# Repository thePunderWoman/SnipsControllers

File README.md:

<h1 align="center">The Snips Controllers</h1>

<p align="center">
  Wireless handheld controllers for R2-D2 droid operation, built to work with the
  <a href="https://github.com/thePunderWoman/Amidala">Amidala</a> control system and firmware.
</p>

<p align="center">
  
</p>

## Status

**Awaiting prototype PCBs.**

The Stackup circuit design, part matching, and layout review are complete; boards are in the ordering/fab pipeline. See [PCB/v1.x/README.md](PCB/v1.x/README.md) for the full hardware writeup and [PCB/v1.x/design-review-2026-08-23.md](PCB/v1.x/design-review-2026-08-23.md)
for the latest design review. PCBs will likely arrive middle to late September. Once the controllers have been validated, we'll start ordering larger runs and make them available for people to buy.

## What they are

The Snips controllers are dual small handheld controllers for driving your droid
builds. These controllers are intended to be small, but powerful controllers that
can be configured via Amidala to do whatever you prefer to do.

## What they offer

Each Snips controller offers 6 face buttons, 2 side buttons on each side, 1 bumper
button, and a precision hall effect analog trigger. They utilize standard thumbsticks
and are specifically designed to work with either gulikit hall effect or tmr kits,
making sure you have no stick drift over time.

Combining all buttons, including center stick, that's 13 button options per controller. Plus, through Amidala each button can support regular press, alt button press, double press, and long press. All told, you have currently up to **52** different programmable options per controller!

Each controller also has a small OLED screen just above the thumbsticks for as much
info as you'd like to see, like power levels, which hand the controller is for, which
droid, volume levels, etc.

## Communication

These controllers are designed to work with Xbee3 modules for long distance secure
communication, but also, since they are powered by ESP32-S3-WROOM-1 modules, they also
support bluetooth and ESP-Now for connectivity. They will be able to swap between droids, as well.

## Batteries

Each controller runs on a single swappable 14500 lithium ion cell (3.7V Li-ion, not 3.2V LiFePO4). We're using 1300 mAh Keeppower cells. The controllers have a built in charging circuit. So you can charge them via USB-C, or just plain swap mid-event if they run out.

Based on datasheet figures (not yet measured on real hardware), a controller with an XBee3 Pro draws about 100 mA, so a 1300 mAh cell should last roughly 11–12 hours of use, or about 8 hours in the worst case.

## Case

The controller case, aka how it looks and feels in the hand is still to be designed, but will be open source, allowing you to make it as unique to your build as you'd like.

## Estimated price

This is yet to be determined since we're so early in the prototype stage, but the pricing will be fully transparent. We will likely try to bundle two controllers with an Amidala board, and hopefully close to at cost with a small donation to charity included.

## Repository layout

| Path | Contents |
|---|---|
| [`src/`](src) | ESP32-S3 firmware (PlatformIO) |
| [`test/`](test) | Native unit tests (no hardware required) |
| [`PCB/`](PCB) | Stackup circuit design, KiCad layout, GPIO reference, and design notes |
| [`scripts/`](scripts) | BOM/part-matching tooling |

## Development

Requires [PlatformIO](https://platformio.org/) (CLI or IDE extension).

```bash
# Build the firmware for V1.x boards (the default)
pio run

# Build the firmware for V2 boards
pio run -e esp32s3_v2

# Run unit tests (no hardware required)
pio test -e native
```

See [CONTRIBUTING.md](CONTRIBUTING.md) for the full contribution workflow.

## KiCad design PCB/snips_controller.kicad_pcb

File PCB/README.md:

# Snips Controller PCB

A wireless handheld controller for R2-D2 droid operation, designed for use at public events and conventions. Communicates with the droid via XBee3 Zigbee radio in a packetized state-report architecture.

The electrical design is in [Stackup KDL](stackup/board.kdl), using the pinned
Stackup library plus a [local thumbstick model](stackup/parts.kdl). The existing [KiCad PCB](snips_controller.kicad_pcb) is linked
through `snips_controller.stackup_sch`; sync it with the Stackup KiCad plugin. Run
`stackup check PCB/stackup/board.kdl` from the repository root before syncing.

## Hardware Overview

| Component | Part | Notes | Layout diagram |
|---|---|---|---|
| MCU | ESP32-S3-WROOM-1 module | Pre-certified: integrated flash, crystal, WiFi/BT radio + antenna. Same MCU family as Amidala. See `GPIO_table.md` for the full support circuitry | — |
| Display | SSD1306 1.3" OLED | 128x64, monochrome, I2C | — |
| Radio | XBee3 Pro (XB3-24Z8UT) | Zigbee 3.0 firmware, U.FL, +19 dBm, SPI mode, THT socket (proto) | — |
| Hall trigger | DRV5055A2QDBZR (SOT-23) | Ratiometric linear hall effect, 3.3V. On the bottom of the board under the trigger magnet; senses the field perpendicular to the board. Trigger calibration accepts either magnet polarity | — |
| Thumbstick | GuliKit hall effect module | Native 3.3V, analog X/Y + click | — |
| Buttons | Omron B3F series | Tactile momentary clicky | — |
| RGB LED | SK6812 NeoPixel-compatible | RMT-driven status indicator; specified supply begins at 3.7 V, but board supplies 3.3 V | — |
| Charger | bq25185 | USB/DC input, power path, 4.2V/500mA | [diagram](diagrams/power_charger_layout.md) |
| Buck | TLV62569 | 3.3V output, 1A | [diagram](diagrams/power_buck_layout.md) |
| Battery | 14500 Li-ion (Keeppower 1300 mAh) | Swappable single cell; 500 mA charge ≈ 0.38C | — |
| Power switch | DMG2305UX + 2N7002 | Soft latch, hybrid hardware+firmware | [diagram](diagrams/power_control_layout.md) |

## Layout Diagrams

Suggested top-copper floorplans for the three sheets with real layout
stakes — a switching regulator, a linear charger with a thermal pad, and
the transistor carrying the whole board's current. Each is checked
against the actual component datasheet, not just the schematic. See
[`diagrams/README.md`](diagrams/README.md) for the full list and how the
files are organized.

- [Buck converter](diagrams/power_buck_layout.md) — `/Power_Buck/*` nets in Stackup
- [Charger](diagrams/power_charger_layout.md) — `/Power_Charger/*` nets in Stackup
- [Power latch](diagrams/power_control_layout.md) — `/Power_Control/*` nets in Stackup

## GPIO Assignment

> See `GPIO_table.md` for the full pin-by-pin table, including
> ESP32-S3-WROOM-1 support circuitry — this section is a summary.

### Reserved — Do Not Use
| Pin | Reason |
|---|---|
| 1, 40, 41 | GND |
| 2 | 3V3 |
| 3 (EN) | Reset/enable, pulled up via R_EN_PU |
| 13 (USB_D-) | Native USB |
| 14 (USB_D+) | Native USB |
| 27 (GPIO0/BOOT) | Boot strapping pin, pulled up via R_BOOT_PU + button |
| 26-32 (internal) | Internal SPI flash — not present on this module at all |
| 33-34 (internal) | Not broken out on the WROOM-1 module |
| 8 (GPIO15) | XBee SPI_ATTN — data-ready interrupt |
| 22 (GPIO18) | XBee ON_SLEEP status input |

Usable with care (strapping pins, sampled at boot): 15 (GPIO3), 16 (GPIO46), 26 (GPIO45).
Clean spares (default JTAG): 34-35 (GPIO41-42). 32/33 from the same group are used by BTN_VOL_DN/BTN_VOL_UP.

The module integrates the WiFi/BT radio, antenna, flash, and crystal
internally — no external wireless component, no bit-banged interface
consuming GPIO, unlike the bare-RP2350A design this replaced.

### SPI (XBee)
| Function | Pin |
|---|---|
| XBee SCK | 18 |
| XBee MOSI | 19 |
| XBee MISO | 20 |
| XBee CS | 21 |
| XBee ON_SLEEP | 22 |
| XBee SPI_ATTN | 8 |

### I2C (OLED)
| Function | Pin |
|---|---|
| SDA | 12 |
| SCL | 17 |

### ADC — ADC1 only (ADC2 is unusable while WiFi is active)
| Function | Pin |
|---|---|
| Analog trigger (DRV5055) | 4 |
| Thumbstick X (GuliKit) | 5 |
| Thumbstick Y (GuliKit) | 6 |
| VSYS battery sense | 7 |

### Digital Inputs / Outputs
| Function | Pin | Notes |
|---|---|---|
| Vol up | 33 | Active low, internal pull-up |
| Vol down | 32 | Active low, internal pull-up |
| Trigger up (mirrored VOL pair, opposite-handed variant) | 9 | Active low, internal pull-up |
| Trigger down (mirrored VOL pair, opposite-handed variant) | 10 | Active low, internal pull-up |
| Digital trigger (bumper) | 11 | Active low, internal pull-up. Two switches in parallel (SW_TRIG_DIG1/2), one at each end of the top edge, so the bumper presses from either side |
| Thumbstick click (KEY) | 23 | Active low, internal pull-up |
| Macro buttons 1-6 | 24, 25, 28, 29, 30, 31 | Active low, internal pull-up — direct-wired, no scan matrix |
| Power button sense | 38 | Input, 3-second hold detect |
| Charge status STAT1 | 39 | Open-drain, 10kΩ pull-up to 3V3 |
| Power latch hold | 36 | Output, HIGH on boot to hold latch |
| RGB LED DIN (SK6812) | 37 | RMT-driven |

### Macro Buttons — Direct-Wired, No Scan Matrix
6 macro buttons, each on its own GPIO with an internal pull-up. No
anti-ghosting diodes or scan firmware needed — ESP32-S3-WROOM-1 has
enough spare GPIO (roughly 8) that the 1-pin savings a 2x3 matrix would
give isn't worth the added complexity, unlike the bare-RP2350A design
(only 1 spare pin) this replaced.

### Spare GPIO
Pins 34-35 (default JTAG, clean) and 15/16/26 (strapping, usable with care).
32/33 from the same JTAG group are used by BTN_VOL_DN/BTN_VOL_UP.

---

## MCU Support Circuitry (ESP32-S3-WROOM-1)

Far simpler than the bare-RP2350A design it replaced — the module
integrates flash, crystal, and the WiFi/BT radio + antenna internally.
What's left: EN pull-up, BOOT pull-up + button, USB series resistors,
3V3 decoupling, and the VSYS battery-sense divider — all standard
ESP32-S3 practice, matching Espressif's own reference designs. See
`GPIO_table.md` for the full component list.

**No longer needed at all:** external QSPI flash chip, crystal + load
caps, core-regulator LC filter, ADC_AVDD RC filter, per-pin IOVDD/DVDD
decoupling network, separate wireless module + its bit-banged interface
+ antenna licensing question.

> **Layout note:** the module's footprint includes the required antenna
> keepout area — keep copper/components out of it per the module's
> datasheet. Much simpler than a custom PCB trace antenna, but still a
> real layout-stage requirement.

---

## Passives & Support Components

### Decoupling Caps
| Component | Value | Notes |
|---|---|---|
| DRV5055 VCC | 100nF ceramic | Close to supply pin |
| GuliKit VCC | 100nF ceramic | Close to supply pin |
| SK6812 VCC | 100nF ceramic | Close to supply pin |
| bq25185 VIN | 10µF + 100nF ceramic | X7R/X5R, 25V rated |
| bq25185 SYS | 10µF + 100nF ceramic | X7R/X5R, 25V rated |
| bq25185 BAT | 10µF ceramic | |
| TLV62569 VIN | 10µF ceramic | |
| TLV62569 VOUT | 22µF ceramic | |
| ESP32-S3-WROOM-1 3V3 | 10µF + 100nF ceramic | Standard module decoupling |

### Pull-up Resistors
| Signal | Value | Notes |
|---|---|---|
| bq25185 STAT1 | 10kΩ | Open-drain, pull up to 3V3 |
| bq25185 TS/MR | 10kΩ to GND | REQUIRED if no thermistor — floating = no charging |
| XBee RESET | 10kΩ to 3V3 | Plus 100Ω + 100nF RC filter at pin |
| I2C SDA/SCL | 4.7kΩ | **DNP for prototyping** — Adafruit #938 has onboard pull-ups. Populate only on final PCB with bare OLED panel |
| ESP32-S3 EN | 10kΩ to 3V3 | Reset/enable |
| ESP32-S3 GPIO0/BOOT | 10kΩ to 3V3 | Plus button to GND to force UF2/download mode |

### Series Resistors
| Signal | Value | Notes |
|---|---|---|
| SK6812 DIN (pin 37) | 300–500Ω | Signal integrity, place close to pad |
| USB D+/D- (pins 13/14) | 27Ω | Between module and external USB-C connector |

### Direct Buttons (all of them — no matrix)
No external components needed. Wire to GND; enable ESP32-S3 internal
pull-ups in firmware. Applies to vol up/down, digital trigger, stick
click, and all 6 macro buttons.

### XBee
Refer to AmidalaShield V1.2 for XBee3 support circuitry. THT socket for prototyping; update footprint to SMT module for final PCB if size requires.

Beyond the 4-wire SPI bus (SCK/MOSI/MISO/CS) and RESET, three more pins are
wired per Amidala's actual netlist: DTR tied to GND, ON_SLEEP and SPI_ATTN
to pins 22/8. SPI_ATTN in particular is the XBee's data-ready interrupt —
needed for reliable SPI transfers, not just a nice-to-have.

---

## Communication Architecture

Controllers communicate with the droid via XBee3 in **packetized state-report** mode. The ESP32-S3 firmware reads all inputs locally (button states, ADC values for analog trigger and thumbstick) and assembles them into a structured payload transmitted periodically over SPI to the XBee3 radio. The receiving AmidalaShield deserializes the packet and interprets controller state.

This approach is preferred over per-signal transmission as it is more efficient, easier to deserialize, and robust to timing issues.

### Network Configuration
- Each droid has its own coordinator with a unique PAN ID
- All coordinators share the same AES encryption key
- Controllers are configured as sleepy end devices (CE=0, SM=1 pin sleep, ET=4 for a 16-minute parent timeout), set at boot by the firmware. Their parent (normally the droid's coordinator) holds downlinks while a controller sleeps, and the controller polls for them every 100 ms while awake
- "Switch droid" functionality is implemented via XBee API commands to leave the current network and rejoin a different PAN ID on demand
- Active droid name and connection status are shown on the OLED display

---

## Bringup Sequence

Recommended bringup order:
1. ESP32-S3-WROOM-1 alone — verify USB enumeration, flash blink sketch, confirm pin 36 latch hold works
2. OLED on I2C — verify I2C on pins 12/17, get something on screen
3. SK6812 RGB LED — verify RMT output on pin 37, cycle colors
4. Buttons — verify direct inputs on pins 9/10/11/23 and all 6 macro buttons (pins 24/25/28/29/30/31)
5. Charge status — verify STAT1 on pin 39 reads correctly
6. DRV5055 + GuliKit thumbstick — verify ADC1 readings on pins 4/5/6
7. XBee over SPI — verify basic communication

---

## Power Architecture

- Battery → bq25185 (charger + power path, 4.2V VBATREG, 500mA) → TLV62569 (3.3V buck) → ESP32-S3-WROOM-1 3V3 and all 3.3V logic
- Power switch: soft latch (DMG2305UX PFET + 2N7002 NFET) controls TLV62569 EN pin
- Boot: press power button → hardware latch enables 3V3 → ESP32-S3-WROOM-1 boots → pin 36 driven HIGH to hold latch
- Shutdown: firmware detects 3-second hold on pin 38 → graceful shutdown → pin 36 LOW → power cut
- bq25185 STAT1 → pin 39 (open-drain, 10kΩ pull-up to 3V3)
- Battery voltage sense → pin 7 via external R_VSYS1/R_VSYS2 divider (reads VSYS/3 via ADC1)
- ESP32-S3-WROOM-1, DRV5055, and GuliKit thumbstick use the 3V3 rail. The SK6812 also uses it, but its 3.7 V minimum supply makes that LED connection out of specification.

No firmware ADC-gating workaround needed for battery sense — WiFi is
fully on-die on ESP32-S3 and doesn't share any exposed GPIO/ADC path
with the VSYS sense pin, unlike the old bit-banged RP2350+CYW43439
design.

## Power Management

Firmware implements tiered power saving:
- **Active**: full brightness OLED, normal polling rate
- **Idle (short timeout)**: OLED dimmed via SSD1306 contrast command
- **Idle (long timeout)**: OLED off
- **Sleep**: MCU sleep, wake on any button press via GPIO interrupt

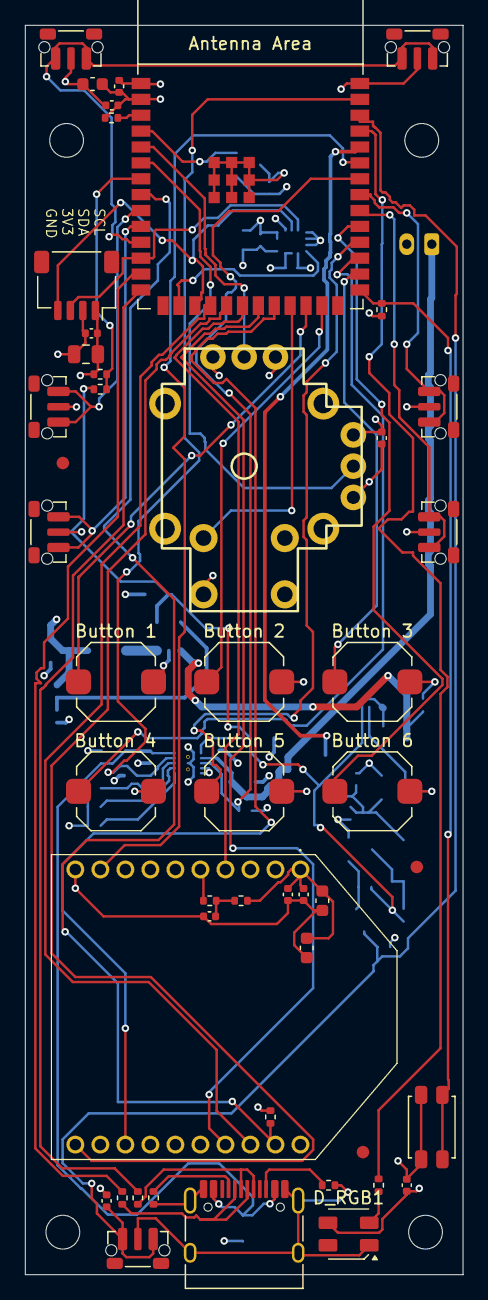
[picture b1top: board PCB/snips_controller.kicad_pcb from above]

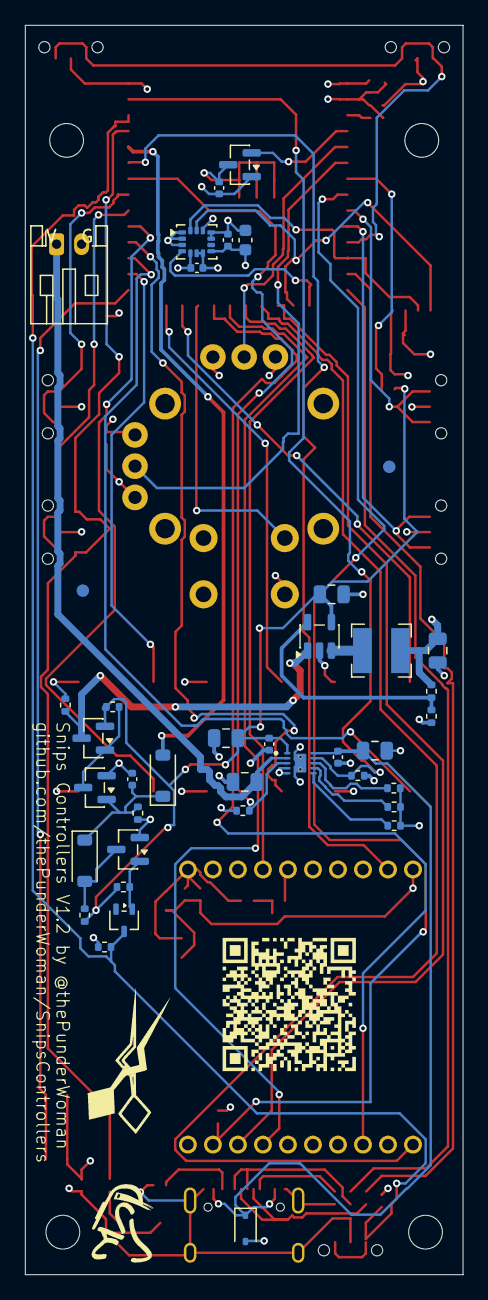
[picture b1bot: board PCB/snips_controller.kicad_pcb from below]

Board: 4 copper layers, 35.0 x 99.9 mm, 95 parts (43 on the bottom side), 57 nets.

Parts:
BT1: PH 2-pin battery RIGHT-ANGLE HORIZONTAL; JST_PH_S2B-PH-K_1x02_P2.00mm_Horizontal
C_3V3_1: 10µF; C_0603_1608Metric
C_3V3_2: 100nF; C_0402_1005Metric
C_3V3_3: 39pF; C_0402_1005Metric
C_BAT1: 10µF; C_0805_2012Metric
C_BUCK_IN1: 10µF; C_0805_2012Metric
C_BUCK_OUT1: 22µF; C_0805_2012Metric
C_DBNC1: 100nF; C_0402_1005Metric
C_HALL1: 100nF; C_0402_1005Metric
C_IMU_1: 100nF; C_0402_1005Metric
C_IMU_2: 2.2µF; C_0603_1608Metric
C_IMU_3: 10nF; C_0402_1005Metric
C_LATCH_G1: 100nF; C_0402_1005Metric
C_OLED_1: 10µF; C_0805_2012Metric
C_OLED_2: 100nF; C_0402_1005Metric
C_RGB1: 100nF; C_0402_1005Metric
C_STICK1: 100nF; C_0402_1005Metric
C_SYS_1: 10µF; C_0805_2012Metric
C_SYS_2: 100nF; C_0402_1005Metric
C_VIN_1: 10µF; C_0805_2012Metric
C_VIN_2: 100nF; C_0402_1005Metric
C_XBEE_RC1: 100nF; C_0402_1005Metric
C_XBEE_VCC1: 100nF; C_0402_1005Metric
C_XBEE_VCC2: 1µF; C_0603_1608Metric
C_XBEE_VCC3: 47pF; C_0402_1005Metric
C_XBEE_VCC4: 10µF; C_0603_1608Metric
D_INV_ISO1: BAT54W-7-F; SOT-323_SC-70
D_OR1, D_OR2: 1N4148W; D_SOD-123
D_RGB1: SK6812MINI-HS-012
D_VBUS_TVS1: TPPESD5V0S1BA; D_SOD-323
FID1, FID2, FID3, FID4, FID5: Fiducial_1mm_Mask2mm
J_STICK1: GuliKit_Thumbstick; GuliKit_HallStick
J_USB1: USB-C; USB_C_Receptacle_HRO_TYPE-C-31-M-12
LOGO1, LOGO2: LOGO
LOGO3: LOGO; R2Builders
L_BUCK1: 2.2µH; L_Bourns-SRN4018
MH1, MH2, MH3, MH4: MountingHole_2.7mm_M2.5
Q_INV1: MMBT3904(RANGE:100-300); SOT-23
Q_LATCH1: AO3400A; SOT-23
Q_PWR1: AO3401A; SOT-23
R_BOOT_PU1: 10kΩ; R_0402_1005Metric
R_BTN_PU1: 100kΩ; R_0402_1005Metric
R_CC1, R_CC2: 5.1kΩ; R_0402_1005Metric
R_EN_PU1: 10kΩ; R_0402_1005Metric
R_FB1: 255kΩ; R_0402_1005Metric
R_FB2: 56.2kΩ; R_0402_1005Metric
R_GATE1: 100kΩ; R_0402_1005Metric
R_INV_BASE1: 100kΩ; R_0402_1005Metric
R_INV_PU1: 100kΩ; R_0402_1005Metric
R_ISET1: 604Ω; R_0402_1005Metric
R_LATCH_G1: 1MΩ; R_0402_1005Metric
R_PWR_EN_PD1: 100kΩ; R_0402_1005Metric
R_RGB1: 470Ω; R_0402_1005Metric
R_STAT1, R_STAT2: 10kΩ; R_0402_1005Metric
R_TS1: 10kΩ; R_0402_1005Metric
R_USB_DM1: 27Ω; R_0402_1005Metric
R_USB_DP1: 27Ω; R_0402_1005Metric
R_VSET1: 18kΩ; R_0402_1005Metric
R_VSYS1: 200kΩ; R_0402_1005Metric
R_VSYS2: 100kΩ; R_0402_1005Metric
R_XBEE_ATTN_PU1: 10kΩ; R_0402_1005Metric
R_XBEE_RC1: 100Ω; R_0402_1005Metric
R_XBEE_RST1: 10kΩ; R_0402_1005Metric
SW_BOOT1: Panasonic_EVQP2; SW_SPST_EVQP2_ShortPushTravel_H2.1mm
SW_MACRO1, SW_MACRO2, SW_MACRO3, SW_MACRO4, SW_MACRO5, SW_MACRO6: 6x6x5mm SMD Tactile; SW_Push_1TS009xxxx-xxxx-xxxx_6x6x5mm
SW_PWR1: SKRTLAE010; SW_Push_1P1T-MP_NO_Horizontal_Alps_SKRTLAE010
SW_THR_DN1: SKRTLAE010; SW_Push_1P1T-MP_NO_Horizontal_Alps_SKRTLAE010
SW_THR_UP1: SKRTLAE010; SW_Push_1P1T-MP_NO_Horizontal_Alps_SKRTLAE010
SW_TRIG_DIG1, SW_TRIG_DIG2: SKRTLAE010; SW_Push_1P1T-MP_NO_Horizontal_Alps_SKRTLAE010
SW_VOL_DN1: SKRTLAE010; SW_Push_1P1T-MP_NO_Horizontal_Alps_SKRTLAE010
SW_VOL_UP1: SKRTLAE010; SW_Push_1P1T-MP_NO_Horizontal_Alps_SKRTLAE010
U_BUCK1: TLV62569DBVR; SOT-23-5
U_CHG1: BQ25185DLHR; IC_BQ25185DLHR
U_HALL1: DRV5055A2QDBZR; SOT-23
U_IMU1: ICM-42670-P; LGA-14_3x2.5mm_P0.5mm_LayoutBorder3x4y
U_MCU1: ESP32-S3-WROOM-1-N8; ESP32-S3-WROOM-1
U_OLED1: Qwiic connector; JST_SH_SM04B-SRSS-TB_1x04-1MP_P1.00mm_Horizontal
U_XBEE1: XBee3; XB324Z8UTJ

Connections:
3V3: C_3V3_1.1, C_3V3_2.1, C_3V3_3.1, C_BUCK_OUT1.1, C_HALL1.1, C_IMU_1.1, C_IMU_2.1, C_IMU_3.1, C_OLED_1.1, C_OLED_2.1, C_RGB1.1, C_STICK1.1, C_XBEE_VCC1.1, C_XBEE_VCC2.1, C_XBEE_VCC3.1, C_XBEE_VCC4.1, D_RGB1.3, J_STICK1.3 (X_HI), J_STICK1.3' (Y_HI), L_BUCK1.2, R_BOOT_PU1.2, R_BTN_PU1.1, R_EN_PU1.2, R_FB1.2, R_STAT1.2, R_STAT2.2, R_XBEE_ATTN_PU1.1, R_XBEE_RST1.1, U_HALL1.1, U_IMU1.5, U_IMU1.8, U_IMU1.12, U_MCU1.2 (3V3), U_OLED1.2 (VCC), U_XBEE1.1 (VCC)
/Accelerometer/I2C_SCL: U_IMU1.13, U_MCU1.17 (GPIO9/TOUCH9/ADC1_CH8/FSPIHD/SUBSPIHD), U_OLED1.4 (SCL)
/Accelerometer/I2C_SDA: U_IMU1.14, U_MCU1.12 (GPIO8/TOUCH8/ADC1_CH7/SUBSPICS1), U_OLED1.3 (SDA)
/Buttons_Direct/BTN_MACRO1: SW_MACRO1.1, U_MCU1.24 (GPIO47/SPICLK_P/SUBSPICLK_P_DIFF)
/Buttons_Direct/BTN_MACRO2: SW_MACRO2.1, U_MCU1.25 (GPIO48/SPICLK_N/SUBSPICLK_N_DIFF)
/Buttons_Direct/BTN_MACRO3: SW_MACRO3.1, U_MCU1.28 (SPIIO6/GPIO35/FSPID/SUBSPID)
/Buttons_Direct/BTN_MACRO4: SW_MACRO4.1, U_MCU1.29 (SPIIO7/GPIO36/FSPICLK/SUBSPICLK)
/Buttons_Direct/BTN_MACRO5: SW_MACRO5.1, U_MCU1.30 (SPIDQS/GPIO37/FSPIQ/SUBSPIQ)
/Buttons_Direct/BTN_MACRO6: SW_MACRO6.1, U_MCU1.31 (GPIO38/FSPIWP/SUBSPIWP)
/Buttons_Direct/BTN_THR_DN: SW_THR_DN1.1, U_MCU1.10 (GPIO17/U1TXD/ADC2_CH6)
/Buttons_Direct/BTN_THR_UP: SW_THR_UP1.1, U_MCU1.9 (GPIO16/U0CTS/ADC2_CH5/XTAL_32K_N)
/Buttons_Direct/BTN_TRIG_DIG: SW_TRIG_DIG1.1, SW_TRIG_DIG2.1, U_MCU1.11 (GPIO18/U1RXD/ADC2_CH7/CLK_OUT3)
/Buttons_Direct/BTN_VOL_DN: SW_VOL_DN1.1, U_MCU1.32 (MTCK/GPIO39/CLK_OUT3/SUBSPICS1)
/Buttons_Direct/BTN_VOL_UP: SW_VOL_UP1.1, U_MCU1.33 (MTDO/GPIO40/CLK_OUT2)
/Hall_Trigger/TRIG_ANALOG: U_HALL1.2, U_MCU1.4 (GPIO4/TOUCH4/ADC1_CH3)
/MCU_Core/BTN_STICK: J_STICK1.a (SW_A), U_MCU1.23 (GPIO21)
/MCU_Core/MCU_BOOT: R_BOOT_PU1.1, SW_BOOT1.2, U_MCU1.27 (GPIO0/BOOT)
/MCU_Core/MCU_EN: R_EN_PU1.1, U_MCU1.3 (EN)
/MCU_Core/PWR_BTN_SENSE: C_DBNC1.1, D_INV_ISO1.3 (K), R_BTN_PU1.2, SW_PWR1.1, U_MCU1.38 (GPIO2/TOUCH2/ADC1_CH1)
/MCU_Core/PWR_HOLD: D_OR2.2 (A), U_MCU1.36 (U0RXD/GPIO44/CLK_OUT2)
/MCU_Core/RGB_DIN: R_RGB1.2, U_MCU1.37 (U0TXD/GPIO43/CLK_OUT1)
/MCU_Core/SPI_MISO: U_MCU1.20 (GPIO12/TOUCH12/ADC2_CH1/FSPICLK/FSPIIO6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), U_XBEE1.4 (SPI_MISO)
/MCU_Core/SPI_MOSI: U_MCU1.19 (GPIO11/TOUCH11/ADC2_CH0/FSPID/FSPIIO5/S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), U_XBEE1.11 (SPI_MOSI)
/MCU_Core/SPI_SCK: U_MCU1.18 (GPIO10/TOUCH10/ADC1_CH9/FSPICS0/FSPIIO4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), U_XBEE1.18 (SPI_CLK)
/MCU_Core/STAT1: R_STAT1.1, U_CHG1.9 (STAT1), U_MCU1.39 (GPIO1/TOUCH1/ADC1_CH0)
/MCU_Core/STAT2: R_STAT2.1, U_CHG1.3 (STAT2), U_MCU1.34 (MTDI/GPIO41/CLK_OUT1)
/MCU_Core/STICK_X: J_STICK1.2 (X_OUT), U_MCU1.5 (GPIO5/TOUCH5/ADC1_CH4)
/MCU_Core/STICK_Y: J_STICK1.2' (Y_OUT), U_MCU1.6 (GPIO6/TOUCH6/ADC1_CH5)
/MCU_Core/USB_DM: J_USB1.A7 (D-), J_USB1.B7 (D-), R_USB_DM1.1
/MCU_Core/USB_DM_MCU: R_USB_DM1.2, U_MCU1.13 (GPIO19/U1RTS/ADC2_CH8/CLK_OUT2/USB_D-)
/MCU_Core/USB_DP: J_USB1.A6 (D+), J_USB1.B6 (D+), R_USB_DP1.1
/MCU_Core/USB_DP_MCU: R_USB_DP1.2, U_MCU1.14 (GPIO20/U1CTS/ADC2_CH9/CLK_OUT1/USB_D+)
/MCU_Core/VSYS_SENSE: R_VSYS1.2, R_VSYS2.1, U_MCU1.7 (GPIO7/TOUCH7/ADC1_CH6)
/MCU_Core/XBEE_ON_SLEEP: U_MCU1.22 (GPIO14/TOUCH14/ADC2_CH3/FSPIWP/FSPIDQS/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), U_XBEE1.13 (ON_SLEEP)
/MCU_Core/XBee_CS: U_MCU1.21 (GPIO13/TOUCH13/ADC2_CH2/FSPIQ/FSPIIO7/S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), U_XBEE1.17 (SPI_SSEL)
/Power_Buck/BUCK_FB: R_FB1.1, R_FB2.1, U_BUCK1.5 (FB)
/Power_Buck/BUCK_SW: L_BUCK1.1, U_BUCK1.3 (SW)
/Power_Buck/PWR_EN: Q_PWR1.3 (D), R_PWR_EN_PD1.1, U_BUCK1.1 (EN)
/Power_Charger/CHG_ISET: R_ISET1.1, U_CHG1.8 (ISET)
/Power_Charger/CHG_TS: R_TS1.1, U_CHG1.6 (TS/MR)
/Power_Charger/CHG_VSET: R_VSET1.1, U_CHG1.7 (ILIM/VSET)
/Power_Control/PWR_BTN_INV_BASE: D_INV_ISO1.1 (A), Q_INV1.1 (B), R_INV_BASE1.2
/Power_Control/PWR_BTN_TRIGGER: D_OR1.2 (A), Q_INV1.3 (C), R_INV_PU1.2
/Power_Control/PWR_GATE: Q_LATCH1.3 (D), Q_PWR1.1 (G), R_GATE1.2
/Power_Control/PWR_LATCH_G: C_LATCH_G1.2, D_OR1.1 (K), D_OR2.1 (K), Q_LATCH1.1 (G), R_LATCH_G1.2
/RGB_LED/RGB_DIN_R: D_RGB1.2, R_RGB1.1
/USB_C/USB_CC1: J_USB1.A5 (CC1), R_CC1.1
/USB_C/USB_CC2: J_USB1.B5 (CC2), R_CC2.1
/XBee/XBEE_RESET: R_XBEE_RC1.2, U_XBEE1.5 (RESET)
/XBee/XBEE_RST_PU: C_XBEE_RC1.1, R_XBEE_RC1.1, R_XBEE_RST1.2
/XBee/XBEE_SPI_ATTN: R_XBEE_ATTN_PU1.2, U_MCU1.8 (GPIO15/U0RTS/ADC2_CH4/XTAL_32K_P), U_XBEE1.19 (SPI_ATTN)
ACCEL_INT1: U_IMU1.4, U_MCU1.16 (GPIO46)
GND: BT1.2, C_3V3_1.2, C_3V3_2.2, C_3V3_3.2, C_BAT1.2, C_BUCK_IN1.2, C_BUCK_OUT1.2, C_DBNC1.2, C_HALL1.2, C_IMU_1.2, C_IMU_2.2, C_IMU_3.2, C_LATCH_G1.1, C_OLED_1.2, C_OLED_2.2, C_RGB1.2, C_STICK1.2, C_SYS_1.2, C_SYS_2.2, C_VIN_1.2, C_VIN_2.2, C_XBEE_RC1.2, C_XBEE_VCC1.2, C_XBEE_VCC2.2, C_XBEE_VCC3.2, C_XBEE_VCC4.2, D_RGB1.1, D_VBUS_TVS1.2 (A2), J_STICK1.1 (X_LO), J_STICK1.1' (Y_LO), J_STICK1.c (SW_C), J_USB1.A1 (GND), J_USB1.A12 (GND), J_USB1.B1 (GND), J_USB1.B12 (GND), J_USB1.SH (SHIELD), Q_INV1.2 (E), Q_LATCH1.2 (S), R_CC1.2, R_CC2.2, R_FB2.2, R_ISET1.2, R_LATCH_G1.1, R_PWR_EN_PD1.2, R_TS1.2, R_VSET1.2, R_VSYS2.2, SW_BOOT1.1, SW_MACRO1.2, SW_MACRO2.2, SW_MACRO3.2, SW_MACRO4.2, SW_MACRO5.2, SW_MACRO6.2, SW_PWR1.2, SW_THR_DN1.2, SW_THR_UP1.2, SW_TRIG_DIG1.2, SW_TRIG_DIG2.2, SW_VOL_DN1.2, SW_VOL_UP1.2, U_BUCK1.2 (GND), U_CHG1.4 (~CE), U_CHG1.5 (GND), U_CHG1.11 (THERMAL_PAD), U_CHG1.12, U_CHG1.13, U_HALL1.3, U_IMU1.1, U_IMU1.2, U_IMU1.3, U_IMU1.6, U_IMU1.7, U_IMU1.10, U_IMU1.11, U_MCU1.1 (GND), U_MCU1.40 (GND), U_MCU1.41 (GND), U_OLED1.1 (GND), U_XBEE1.10 (GND)
VBAT: BT1.1, C_BAT1.1, U_CHG1.2 (BAT)
VBUS: C_VIN_1.1, C_VIN_2.1, D_VBUS_TVS1.1 (A1), J_USB1.A4 (VBUS), J_USB1.A9 (VBUS), J_USB1.B4 (VBUS), J_USB1.B9 (VBUS), U_CHG1.10 (IN)
VSYS: C_BUCK_IN1.1, C_SYS_1.1, C_SYS_2.1, Q_PWR1.2 (S), R_GATE1.1, R_INV_BASE1.1, R_INV_PU1.1, R_VSYS1.1, U_BUCK1.4 (VIN), U_CHG1.1 (SYS)
XBEE_SLEEP_RQ: U_MCU1.35 (MTMS/GPIO42), U_XBEE1.9 (DTR)

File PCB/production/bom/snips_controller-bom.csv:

"Id";"Designator";"Footprint";"Quantity";"Designation";"Supplier and ref";
1;"BT1";"JST_PH_S2B-PH-K_1x02_P2.00mm_Horizontal";1;"PH 2-pin battery RIGHT-ANGLE HORIZONTAL";;;
2;"C_3V3_1, C_XBEE_VCC4";"C_0603_1608Metric";2;"10µF";;;
3;"C_3V3_2, C_DBNC1, C_HALL1, C_IMU_1, C_LATCH_G1, C_OLED_2, C_RGB1, C_STICK1, C_SYS_2, C_VIN_2, C_XBEE_RC1, C_XBEE_VCC1";"C_0402_1005Metric";12;"100nF";;;
4;"C_3V3_3";"C_0402_1005Metric";1;"39pF";;;
5;"C_BAT1, C_BUCK_IN1, C_OLED_1, C_SYS_1, C_VIN_1";"C_0805_2012Metric";5;"10µF";;;
6;"C_BUCK_OUT1";"C_0805_2012Metric";1;"22µF";;;
7;"C_IMU_2";"C_0603_1608Metric";1;"2.2µF";;;
8;"C_IMU_3";"C_0402_1005Metric";1;"10nF";;;
9;"C_XBEE_VCC2";"C_0603_1608Metric";1;"1µF";;;
10;"C_XBEE_VCC3";"C_0402_1005Metric";1;"47pF";;;
11;"D_INV_ISO1";"SOT-323_SC-70";1;"BAT54W-7-F";;;
12;"D_OR1, D_OR2";"D_SOD-123";2;"1N4148W";;;
13;"D_RGB1";"SK6812MINI-HS-012";1;"SK6812MINI-HS-012";;;
14;"D_VBUS_TVS1";"D_SOD-323";1;"TPPESD5V0S1BA";;;
15;"J_USB1";"USB_C_Receptacle_HRO_TYPE-C-31-M-12";1;"USB-C";;;
16;"L_BUCK1";"L_Bourns-SRN4018";1;"2.2µH";;;
17;"Q_INV1";"SOT-23";1;"MMBT3904(RANGE:100-300)";;;
18;"Q_LATCH1";"SOT-23";1;"AO3400A";;;
19;"Q_PWR1";"SOT-23";1;"AO3401A";;;
20;"R_BOOT_PU1, R_EN_PU1, R_STAT1, R_STAT2, R_TS1, R_XBEE_ATTN_PU1, R_XBEE_RST1";"R_0402_1005Metric";7;"10kΩ";;;
21;"R_BTN_PU1, R_GATE1, R_INV_BASE1, R_INV_PU1, R_PWR_EN_PD1, R_VSYS2";"R_0402_1005Metric";6;"100kΩ";;;
22;"R_CC1, R_CC2";"R_0402_1005Metric";2;"5.1kΩ";;;
23;"R_FB1";"R_0402_1005Metric";1;"255kΩ";;;
24;"R_FB2";"R_0402_1005Metric";1;"56.2kΩ";;;
25;"R_ISET1";"R_0402_1005Metric";1;"604Ω";;;
26;"R_LATCH_G1";"R_0402_1005Metric";1;"1MΩ";;;
27;"R_RGB1";"R_0402_1005Metric";1;"470Ω";;;
28;"R_USB_DM1, R_USB_DP1";"R_0402_1005Metric";2;"27Ω";;;
29;"R_VSET1";"R_0402_1005Metric";1;"18kΩ";;;
30;"R_VSYS1";"R_0402_1005Metric";1;"200kΩ";;;
31;"R_XBEE_RC1";"R_0402_1005Metric";1;"100Ω";;;
32;"SW_BOOT1";"SW_SPST_EVQP2_ShortPushTravel_H2.1mm";1;"Panasonic_EVQP2";;;
33;"SW_MACRO1, SW_MACRO2, SW_MACRO3, SW_MACRO4, SW_MACRO5, SW_MACRO6";"SW_Push_1TS009xxxx-xxxx-xxxx_6x6x5mm";6;"6x6x5mm SMD Tactile";;;
34;"SW_PWR1, SW_THR_DN1, SW_THR_UP1, SW_TRIG_DIG1, SW_VOL_DN1, SW_VOL_UP1";"SW_Push_1P1T-MP_NO_Horizontal_Alps_SKRTLAE010";6;"SKRTLAE010";;;
35;"U_BUCK1";"SOT-23-5";1;"TLV62569DBVR";;;
36;"U_CHG1";"IC_BQ25185DLHR";1;"BQ25185DLHR";;;
37;"U_IMU1";"LGA-14_3x2.5mm_P0.5mm_LayoutBorder3x4y";1;"ICM-42670-P";;;
38;"U_MCU1";"ESP32-S3-WROOM-1";1;"ESP32-S3-WROOM-1-N8";;;
39;"U_OLED1";"JST_SH_SM04B-SRSS-TB_1x04-1MP_P1.00mm_Horizontal";1;"Qwiic connector";;;

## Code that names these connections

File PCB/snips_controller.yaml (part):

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# NET LEGEND
# ---------------------------------------------------------------------------
# VBUS        - 5V USB input from USB-C connector
# VSYS        - Battery/charger system output (bq25185 SYS pin), ~3.7-4.5V
# 3V3         - Regulated 3.3V output from TLV62569 buck
# GND         - Ground
# VBAT        - Battery positive terminal
# USB_DP_MCU/USB_DM_MCU - USB D+/D- data lines (native USB, U_MCU pins 14/13)
# I2C_SDA     - I2C data (pin 12) — OLED
# I2C_SCL     - I2C clock (pin 17) — OLED
# SPI_SCK     - XBee SPI clock (pin 18)
# SPI_MOSI    - XBee SPI MOSI (pin 19)
# SPI_MISO    - XBee SPI MISO (pin 20)
# XBee_CS     - XBee SPI chip select (pin 21)
# XBEE_ON_SLEEP - XBee ON/~SLEEP status, host input (pin 22)
# XBEE_SPI_ATTN - XBee SPI data-ready interrupt (pin 8)
# TRIG_ANALOG - Analog trigger output from DRV5055 (pin 4, ADC1_CH3)
# STICK_X     - Thumbstick X axis (pin 5, ADC1_CH4)
# STICK_Y     - Thumbstick Y axis (pin 6, ADC1_CH5)
# STAT1       - bq25185 charge status pin 1 (open-drain, pin 39)
# STAT2       - bq25185 charge status pin 2 (open-drain, pin 34) — combined
#               with STAT1 to fully decode charging/done/fault states
# RGB_DIN     - WS2812 NeoPixel data in (pin 37)
# PWR_EN      - TLV62569 EN signal, driven by soft latch PFET drain
# PWR_GATE    - PFET gate node (pulled HIGH by default = off)
# PWR_LATCH_G - NFET latch gate (driven by button OR PWR_HOLD)
# PWR_HOLD    - Pin 36 output to OR diode, holds latch after boot
# PWR_BTN_SENSE - Power button junction: R_BTN_PU/R_PWR_SENSE divider
#               midpoint, pulled to VSYS, button pulls to GND, feeds pin 38
# BTN_*       - Individual button nets (pulled up internally, wired to GND),
#               includes the 6 macro buttons — direct-wired, no scan matrix
# MCU_EN      - EN (reset) pin, pulled up via R_EN_PU
# MCU_BOOT    - GPIO0/BOOT strapping pin, pulled up via R_BOOT_PU, button
#               pulls low to enter UF2/download mode
# VSYS_SENSE  - Divide-by-3 VSYS sense into pin 7 (ADC1_CH6), via
#               R_VSYS1/R_VSYS2

# ---------------------------------------------------------------------------
# RESERVED GPIO — DO NOT USE
# ---------------------------------------------------------------------------
# Pin 3  (EN)      - reset/enable, pulled up via R_EN_PU
# Pin 27 (GPIO0)   - BOOT strapping pin, pulled up via R_BOOT_PU + button
# Pin 13 (GPIO19)  - USB_D-  (native USB)
# Pin 14 (GPIO20)  - USB_D+  (native USB)
# Pins 1, 40, 41   - GND
# Pin 2            - 3V3
#
# Use with care if ever needed (strapping pins, sampled at boot):
# Pin 15 (GPIO3), Pin 16 (GPIO46), Pin 26 (GPIO45)
#
# Spare (clean, no caveats) — default JTAG, fully reusable as plain GPIO:
# Pin 32 (GPIO39/MTCK), Pin 33 (GPIO40/MTDO), Pin 34 (GPIO41/MTDI),
# Pin 35 (GPIO42/MTMS)

# ---------------------------------------------------------------------------
groups:
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  # VIN    <- VBUS (5V USB)
  # SYS    -> VSYS rail
  # BAT    <-> VBAT
  # STAT1  -> MCU pin 39 (GPIO1, open-drain, 10kΩ pull-up to 3V3)
  # STAT2  -> MCU pin 34 (GPIO41, open-drain, 10kΩ pull-up to 3V3) — STAT1+
  #           STAT2 together fully decode charging/done/fault states
  # ISET   -> R_ISET to GND. ICHG = 300 AΩ / RISET.
  #           RISET = 600Ω -> ~500mA charge current
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      - net: VBAT
        pins: [U_CHG:BAT, C_BAT:1, PF_VBAT:1]
      - net: STAT1
        pins: [U_CHG:STAT1, R_STAT1:1, U_MCU:39]
      - net: STAT2
        pins: [U_CHG:STAT2, R_STAT2:1, U_MCU:34]
      - net: 3V3
        pins: [R_STAT1:2, R_STAT2:2]
      - net: GND
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        pins: [Q_LATCH:S, R_LATCH_G:1, C_DBNC:2, SW_PWR:2]
      # PWR_BTN_NODE and PWR_BTN_SENSE are the same physical node (R_BTN_PU/
      # R_PWR_SENSE divider midpoint, also where the button pulls to GND) —
      # standardized on one label (PWR_BTN_SENSE) to avoid an ERC ambiguous-
      # net-name warning.
      - net: PWR_BTN_SENSE
        pins: [SW_PWR:1, R_BTN_PU:2, C_DBNC:1, D_OR1:A, R_PWR_SENSE:1, U_MCU:38]
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  # KiCad library (github.com/espressif/kicad-libraries), not hand-authored.
  #
  # Pins referenced by number, not name — the module's pins are heavily
  # multi-function (e.g. pin 4 is "GPIO4/TOUCH4/ADC1_CH3") and numbers are
  # unambiguous. GPIO26-32 are internally wired to the module's own flash
  # and are not present on this symbol at all; GPIO33/34 exist on the bare
  # chip but aren't broken out on the WROOM-1 module either.
  #
  # EN and GPIO0 (BOOT) both have internal weak pull-ups, but external
  # 10kΩ pull-ups are standard, reliable practice for both (matches every
  # real ESP32-S3 reference design, including Espressif's own DevKitC).
  # GPIO0 additionally gets a button to pull it low at boot, exactly like
  # the old RP2350 BOOTSEL pattern, just renamed to match ESP32 convention.
  #
  # ADC signals deliberately use ADC1-only pins (4/5/6/7) — ADC2 is
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      - net: SPI_SCK
        pins: [U_MCU:18, U_XBEE:SPI_CLK]
      - net: SPI_MOSI
        pins: [U_MCU:19, U_XBEE:SPI_MOSI]
      - net: SPI_MISO
        pins: [U_MCU:20, U_XBEE:SPI_MISO]
      - net: XBee_CS
        pins: [U_MCU:21, U_XBEE:SPI_SSEL]
      - net: XBEE_ON_SLEEP
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        pins: [U_MCU:30, SW_MACRO5:1]
      - net: BTN_MACRO6
        pins: [U_MCU:31, SW_MACRO6:1]
      # VSYS battery-voltage sense: divide-by-3 into ADC1_CH6 (pin 7)
      - net: VSYS_SENSE
        pins: [R_VSYS1:2, R_VSYS2:1, U_MCU:7]
      - net: GND
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        pins: [U_MCU:16, U_ACCEL:INT1]
      # Spare GPIO: 15/26 usable-with-care (strapping), 34 clean (default
      # JTAG, fully reusable as plain GPIO; 32/33 from the same clean JTAG
      # group now used above for BTN_VOL_UP/BTN_VOL_DN). Pins 16/35 (also
      # strapping/clean-JTAG) are now spoken for above.
      - no_connect: [U_MCU:15, U_MCU:26, U_MCU:34]

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      # DTR (SLEEP_RQ) diverges from Amidala's netlist on purpose: Amidala
      # ties it straight to GND (permanently deasserted, no host-commanded
      # sleep). This board wires it to a host GPIO instead (see
      # XBEE_SLEEP_RQ net above, MCU pin 35/GPIO42) so firmware can put
      # the module into pin sleep during low-power mode rather than
      # keeping the radio powered the whole time.
      # Remaining auxiliary pins unused: DOUT/DIN(secondary UART),
      # RSSI_PWM, PWM1, [RESERVED]x2, CTS, ASSOCIATE, RTS, AD0
      - no_connect: [U_XBEE:2, U_XBEE:3, U_XBEE:6, U_XBEE:7, U_XBEE:8,
                     U_XBEE:12, U_XBEE:14, U_XBEE:15, U_XBEE:16, U_XBEE:20]
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      - net: RGB_DIN_R
        pins: [R_RGB:1]
      - net: RGB_DIN_R
        pins: [D_RGB:DIN]
      # DOUT: chains to the next LED in a strip — no next LED in this design
      - no_connect: [D_RGB:DOUT]

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#    on-die here and doesn't share any exposed GPIO/ADC path.
#
# 7. ESP32-S3-WROOM-1 powered via its 3V3 pin (pin 2) directly — the module
#    has no separate VSYS-style pin, its own internal regulation is only
#    for the RF/digital core, not a board-level supply input.
#
# 8. EN (pin 3) and GPIO0/BOOT (pin 27) are strapping pins, each pulled up
#    externally via 10kΩ (R_EN_PU/R_BOOT_PU) per standard ESP32-S3
#    practice. GPIO0 additionally has SW_BOOT to pull it low at boot to
#    force UF2/download mode. GPIO3/45/46 are also strapping pins — left
#    unconnected (see RESERVED GPIO), fine to use later but avoid anything
#    that toggles during boot.
#
# 9. CE pin on bq25185 tied to GND (always enable charging).
#
# 10. Power control: PWR_HOLD (pin 36) must be driven HIGH as the very
#     first instruction in firmware or power cuts when user releases the
#     power button.
#
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# 12. Macro buttons are direct-wired (no scan matrix, no anti-ghosting
#     diodes needed) — see MCU_Core section for why.
#
# 13. STAT2 on bq25185 wired to R_STAT2 (10kΩ pull-up to 3V3) and MCU pin 34
#     (GPIO41). STAT1 alone only tells firmware "charging vs not" — STAT1+
#     STAT2 together fully decode the charger's 4 states (charging, done,
#     recoverable fault, latched fault) per the datasheet's status table.
#
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#
# 16. Spare GPIO: pins 15/16/26 (strapping, usable with care) and pins
#     34/35 (default JTAG, cleanly reusable; 32/33 from the same group now
#     used for BTN_VOL_UP/BTN_VOL_DN). See RESERVED GPIO header.

sheets:
  USB_C:
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
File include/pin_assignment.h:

#pragma once

// Raw GPIO pin assignments for the Snips Controller. Values here are
// Arduino GPIO numbers (e.g. 16 means GPIO16), not the module's physical
// pin numbers used in the PCB docs.
//
// Two boards, picked at build time:
//   - V1.x (ESP32-S3-WROOM-1, `pio run -e esp32s3`): a 1:1 mirror of
//     PCB/v1.x/GPIO_table.md. The XBee is on SPI.
//   - V2 (ESP32-S3-MINI-1U, `pio run -e esp32s3_v2`, which defines
//     SNIPS_BOARD_V2): a 1:1 mirror of PCB/v2.x/snips/GPIO_table.md. The
//     XBee is on an optional carrier board, over UART.
// The two maps are not interchangeable: V1 firmware on a V2 board would
// read the wrong buttons. Cross-reference the GPIO tables for the
// physical-pin-to-GPIO mapping, reserved pins, and the rationale behind
// each assignment.

namespace PinAssignment {

#if defined(SNIPS_BOARD_V2)

// ---- UART (XBee carrier, pads 1-6) ----------------------------------------
// The ESP32 transmits on the XBee's DIN and receives on its DOUT. CTS is
// the XBee's output (low = ready); RTS is its input. With no carrier fitted
// these float, so the transport pulls CTS, DOUT and ON/SLEEP up and treats
// CTS high as "no XBee" (see xbee_uart.h).
constexpr int kXbeeUartTx = 35;   // carrier pad 2, XBee DIN
constexpr int kXbeeUartRx = 36;   // carrier pad 3, XBee DOUT
constexpr int kXbeeCts = 34;      // carrier pad 1
constexpr int kXbeeRts = 39;      // carrier pad 4
constexpr int kXbeeOnSleep = 41;  // carrier pad 5
// Carrier pad 6. Drive open drain only: low, or released (input). The
// pull-up is on the carrier.
constexpr int kXbeeReset = 42;
// Carrier pad 7, XBee DTR/SLEEP_RQ. Low = stay awake; set it as one of the
// first instructions in setup(), same as on V1.
constexpr int kXbeeSleepRq = 1;

// ---- I2C (OLED, ICM-42670-P IMU) ------------------------------------------
constexpr int kI2cSda = 12;
constexpr int kI2cScl = 13;

// ---- IMU interrupt (ICM-42670-P INT1) --------------------------------------
// No longer on a strap pin, unlike V1's GPIO46.
constexpr int kAccelInterrupt = 37;

// ---- ADC1 (analog trigger, thumbstick, battery sense) -----------------------
constexpr int kAnalogTrigger = 9;
constexpr int kThumbstickX = 7;
constexpr int kThumbstickY = 6;
constexpr int kVsysSense = 10;  // divide-by-3, same as V1

// ---- Digital buttons -------------------------------------------------------
// Same names and meanings as V1; only the GPIOs moved. V2 has one bumper.
constexpr int kVolUp = 38;
constexpr int kVolDown = 40;
constexpr int kTriggerUp = 33;
constexpr int kTriggerDown = 18;
constexpr int kDigitalTrigger = 47;  // bumper
constexpr int kThumbstickClick = 17;
constexpr int kMacro1 = 16;
constexpr int kMacro2 = 5;
constexpr int kMacro3 = 4;
constexpr int kMacro4 = 11;
constexpr int kMacro5 = 8;
constexpr int kMacro6 = 2;

// ---- Power -------------------------------------------------------------------
// RTC-domain pin, like V1's GPIO2.
constexpr int kPowerButtonSense = 21;
// RXD0. Its pull-up holds the latch through any reset or USB upload.
// Firmware drives it high early in boot and low to power off, and must
// never start UART0 receive on it (Serial is native USB, so it doesn't).
constexpr int kPowerLatchHold = 44;

// ---- Charging (bq25185) ----------------------------------------------------
constexpr int kChargeStat1 = 15;
constexpr int kChargeStat2 = 14;

// ---- RGB status LED (SK6812, RMT-driven) -------------------------------------
// Moved off TXD0, which prints the boot log.
constexpr int kRgbLedData = 48;

#else  // V1.x


// ---- SPI (XBee) --------------------------------------------------------
constexpr int kXbeeSpiSck = 10;
constexpr int kXbeeSpiMosi = 11;
constexpr int kXbeeSpiMiso = 12;
constexpr int kXbeeSpiCs = 13;
constexpr int kXbeeOnSleep = 14;
constexpr int kXbeeSpiAttn = 15;
// XBee DTR/SLEEP_RQ, driven by the host to request pin sleep (drive high =
// request sleep once idle, low = wake immediately). Was hardwired to GND
// (permanently deasserted) on earlier revisions; must be set to a known
// level (low = stay awake) as one of the first instructions in setup(),
// same idiom as kPowerLatchHold, since it's replacing a hard GND tie
// rather than a pull resistor.
constexpr int kXbeeSleepRq = 42;

// ---- I2C (OLED, ICM-42670-P IMU or QMA6100P accelerometer) -------------
constexpr int kI2cSda = 8;
constexpr int kI2cScl = 9;

// ---- Accelerometer (ICM-42670-P or QMA6100P, shares the I2C bus above) --
// INT1 output, wired so the MCU can light-sleep and wake on the
// accelerometer's hardware motion interrupt instead of polling. Strapping
// pin (GPIO46, boot message control only) — safe here since either chip's
// interrupt output stays inactive (never driven high) through boot until
// firmware configures it.
constexpr int kAccelInterrupt = 46;

// ---- ADC1 (analog trigger, thumbstick, battery sense) -------------------
constexpr int kAnalogTrigger = 4;
constexpr int kThumbstickX = 5;
constexpr int kThumbstickY = 6;
constexpr int kVsysSense = 7;

// ---- Digital buttons -----------------------------------------------------
// "Vol" and "Trigger" up/down are two generic, symmetric button pairs —
// see PCB/v1.x/GPIO_table.md. What each pair does is assigned by Amidala, not
// fixed in firmware; these names just match the PCB's schematic/net names.
constexpr int kVolUp = 40;
constexpr int kVolDown = 39;
constexpr int kTriggerUp = 16;
constexpr int kTriggerDown = 17;
constexpr int kDigitalTrigger = 18;  // bumper
constexpr int kThumbstickClick = 21;
constexpr int kMacro1 = 47;
constexpr int kMacro2 = 48;
constexpr int kMacro3 = 35;
constexpr int kMacro4 = 36;
constexpr int kMacro5 = 37;
constexpr int kMacro6 = 38;

// ---- Power ---------------------------------------------------------------
constexpr int kPowerButtonSense = 2;
constexpr int kPowerLatchHold = 44;

// ---- Charging (bq25185) ---------------------------------------------------
constexpr int kChargeStat1 = 1;
constexpr int kChargeStat2 = 41;

// ---- RGB status LED (SK6812/WS2812, RMT-driven) ---------------------------
constexpr int kRgbLedData = 43;

#endif  // SNIPS_BOARD_V2

}  // namespace PinAssignment

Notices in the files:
parts and their libraries:
Adapted from dbenoy/thumbstick-breakout (CC-BY-SA 4.0, Copyright (c) Daniel Benoy), which itself used the C&K THB001P datasheet for dimensions.
Adapted from dbenoy/thumbstick-breakout (CC-BY-SA 4.0, Copyright (c) Daniel Benoy).
